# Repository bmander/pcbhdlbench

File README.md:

# pcbhdl-bench

Rosetta Code for PCB HDLs. Each case describes a circuit board in plain words: its parts, its
nets, its outline and what its layout must respect. Each toolchain writes the board in its own
language and lays it out, and every result is graded the same way, from the copper it drew.

Results: **[bmander.github.io/pcbhdlbench](https://bmander.github.io/pcbhdlbench/)**.

Modelled on [brep-bench](https://github.com/bmander/brep-bench), which does the same for B-rep
kernels.

**Status: early.** 82 cases in 11 categories, 23 of them specified down to the netlist and the
rest one-paragraph sketches. The harness grades fourteen of the checks (`parts`, `connectivity`,
`rules`, `outline`, `fixed`, `side`, `layers`, `near`, `replica`, `loop`, `apart`, `copper`,
`width`, `vias`) and refusals, which is what those 23 cases ask. Two toolchains are entered, tscircuit and netsmith, and three routers (Freerouting, fastroute and
KiCadRoutingTools) on the cases that place every part; their results are on the site.

## Why

Hardware description languages for circuit boards keep appearing (tscircuit, atopile, Zener, SKiDL,
JITX, Polymorphic Blocks), and most stop at the netlist. The step after it, from a design to a
placed and routed board, is the one now being handed to autorouters and LLM agents. The benchmarks
of that step ([a survey](landscape.json), on the site as *Prior work*) each give one canonical file
to an agent or a router. None compares the languages, and none isolates the difficulties.

## Cases

| Category | Asks |
| --- | --- |
| `basics` | Can the toolchain read a design, place, route and write a board at all |
| `placement` | Parts near a pin, on an edge, out of a keepout, under a ceiling |
| `routing` | Crossings, buses, channels, mazes, QFN and BGA fanouts |
| `power` | Width for current, pours and planes, hot loops, Kelvin and star connections |
| `highspeed` | Differential pairs, impedance, matched lengths, return paths |
| `rules` | Clearance, creepage, annular rings, edges, silkscreen |
| `outline` | Round, L-shaped and slotted boards; Uno shield, Pi HAT, M.2 |
| `reuse` | A module laid out once and used many times, congruently |
| `parametric` | Rings, grids and ladders that follow from a number |
| `unsatisfiable` | Boards that cannot be made: the right answer is a refusal |
| `integration` | Real boards, from a 555 blinker to a single-board computer |

A case is `cases/<category>/<name>.md`: a TOML header, then the description. A *specified* case's
header holds its outline, parts and nets ([`patterns.toml`](patterns.toml) has the land patterns,
[`rules.toml`](rules.toml) the rule sets); a *sketch* has only its title, layers and the checks it
would name.

## Grading, as proposed

A runner writes a KiCad `.kicad_pcb`. The harness reads its geometry and nothing else, works out
from the copper what is joined to what, and checks what the case names: always that the parts are
there, that the copper joins exactly the case's nets, that the rule set holds and that everything is
inside the outline; then, by case, fixed positions, distances, keepouts, widths, lengths, pairs,
impedance, pours, creepage, loop area, congruent replicas. **Pass** is every check. **Placed** is a
legal placement not fully routed. **Refused** ranks above **wrong**. See [SPEC.md](SPEC.md).

## Running it

```bash
(cd toolchains/tscircuit && npm install)   # tscircuit, and bun, which its CLI runs on
# netsmith, from source (it has no binary for an Intel Mac); its chips use an installed KiCad's footprints
git clone https://github.com/noahdgrant/netsmith toolchains/netsmith/upstream
(cd toolchains/netsmith/upstream && NETSMITH_SKIP_WEB=1 CARGO_TARGET_DIR=../target cargo build --release -p netsmith-cli --locked)
# the routers; all three need an installed KiCad, whose Python writes and reads Specctra and fills zones
gh release download v2.1.0 -R freerouting/freerouting -p freerouting-2.1.0.jar -D toolchains/freerouting   # runs on Java 21
gh release download v0.1.14 -R parisxmas/fastroute -p 'fastroute-0.1.14-macos-x64.tar.gz' -D toolchains/fastroute
mkdir -p toolchains/fastroute/bin && tar -xzf toolchains/fastroute/*.tar.gz -C toolchains/fastroute/bin
git clone https://github.com/drandyhaas/KiCadRoutingTools toolchains/krt/upstream
python3 -m venv toolchains/krt/venv && toolchains/krt/venv/bin/pip install numpy scipy shapely Pillow
(cd toolchains/krt/upstream && ../venv/bin/python build_router.py)
python3 harness/run.py                     # run every specified case: results/
python3 harness/site.py                    # render the board: site/
python3 -m http.server -d site             # serve it
```

The harness is Python 3.11+, standard library only; a runner needs its toolchain (tscircuit's needs
Node). `run.py --case basics/rc-lowpass` runs one case, `--toolchain NAME` one toolchain. Each
board is kept at `results/<toolchain>/<case>/board.kicad_pcb`, and the site draws it from there.

## The playground

`playground/` is a page for watching autorouters work: place pads, name nets, pick a strategy
(Lee, bidirectional, A*, Hadlock, rip-up and reroute, negotiated congestion, simulated annealing),
with tracks square or at 45°, and optionally improved afterwards by a cost of length, vias and turns, and see the search spread and the tracks
laid. The routers are a small Rust crate with no dependencies, `playground/router`, compiled to
WebAssembly behind a C ABI; the page around it is plain JavaScript and a canvas. The cases that
place every part of a two-layer board are among the boards it starts from, and so are three
boards of open hardware with their routing taken away (`playground/boards`, which says whose
they are and under what licences): an Arduino Uno R3, the Castor & Pollux synthesiser's
mainboard and the Corne keyboard.

```bash
cargo test --release --manifest-path playground/router/Cargo.toml
cargo build --release --target wasm32-unknown-unknown --manifest-path playground/router/Cargo.toml
python3 harness/site.py     # copies the page and the module to site/playground/
```

A board can be routed with no page, for timing: `python3 playground/boards/floats.py
playground/boards/corne-keyboard.json /tmp/corne.f32`, then `cargo run --release --example route
--manifest-path playground/router/Cargo.toml -- /tmp/corne.f32 6 1 300` (the strategy's number, 1
for diagonal steps, and the seconds to go on for).

These are teaching routers on a coarse grid, not entrants: they are not on the routers' board.

## Adding a toolchain

Write a runner (`<command> <case id> <out dir>`, see [SPEC.md](SPEC.md#a-runner)) and an
implementation of each specified case under `toolchains/<name>/`, and give the toolchain's entry
in `toolchains.json` its `command`, `version` and `source`. `toolchains/tscircuit` and
`toolchains/netsmith` are the two to copy from. A toolchain that numbers its own parts says which
is which in its `result.json` (`refs`), as netsmith's runner does.

## Open questions

- **Who is entered.** As written, a toolchain: a language with whatever places and routes for it,
  an LLM agent included. The cases would serve as well for agents alone, each given the case and
  any language it likes.
- **Land patterns.** The bench defines its own in `patterns.toml` and checks pads, not names. A
  large case will need a few hundred; importing a subset of KiCad's library by name may be saner.
- **What "placed" is worth**, when most of these languages cannot route.
- **Electrical checks beyond geometry.** Impedance and creepage are computed from geometry here;
  nothing is simulated.

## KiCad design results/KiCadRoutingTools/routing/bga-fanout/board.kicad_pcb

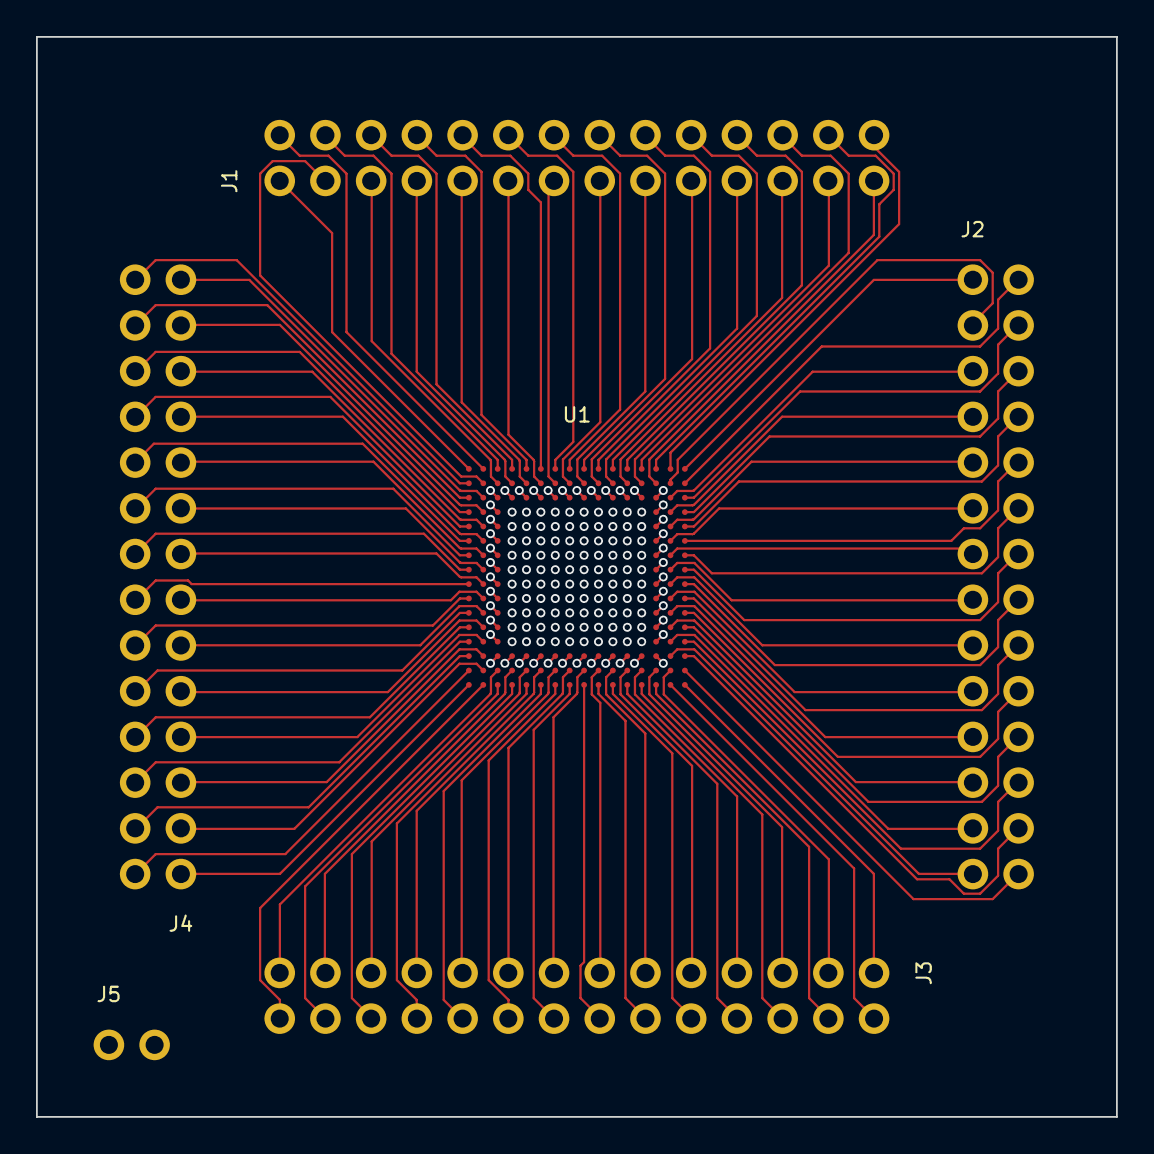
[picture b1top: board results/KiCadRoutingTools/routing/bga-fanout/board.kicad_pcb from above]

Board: 4 copper layers, 60.0 x 60.0 mm, 6 parts (0 on the bottom side), 114 nets.

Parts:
J1, J2, J3, J4: HDR_2x14_2.54
J5: HDR_1x2_2.54
U1: BGA-256

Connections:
A1: J1.1, U1.A1
A2: J1.2, U1.A2
A3: J1.4, U1.A3
A4: J1.6, U1.A4
A5: J1.8, U1.A5
A6: J1.10, U1.A6
A7: J1.12, U1.A7
A8: J1.14, U1.A8
A9: J1.16, U1.A9
A10: J1.18, U1.A10
A11: J1.20, U1.A11
A12: J1.22, U1.A12
A13: J1.24, U1.A13
A14: J1.26, U1.A14
A15: J1.28, U1.A15
A16: J2.1, U1.A16
B1: J4.28, U1.B1
B2: J1.3, U1.B2
B3: J1.5, U1.B3
B4: J1.7, U1.B4
B5: J1.9, U1.B5
B6: J1.11, U1.B6
B7: J1.13, U1.B7
B8: J1.15, U1.B8
B9: J1.17, U1.B9
B10: J1.19, U1.B10
B11: J1.21, U1.B11
B12: J1.23, U1.B12
B13: J1.25, U1.B13
B14: J1.27, U1.B14
B15: J2.3, U1.B15
B16: J2.2, U1.B16
C1: J4.26, U1.C1
C2: J4.27, U1.C2
C15: J2.5, U1.C15
C16: J2.4, U1.C16
D1: J4.24, U1.D1
D2: J4.25, U1.D2
D15: J2.7, U1.D15
D16: J2.6, U1.D16
E1: J4.22, U1.E1
E2: J4.23, U1.E2
E15: J2.9, U1.E15
E16: J2.8, U1.E16
F1: J4.20, U1.F1
F2: J4.21, U1.F2
F15: J2.11, U1.F15
F16: J2.10, U1.F16
G1: J4.18, U1.G1
G2: J4.19, U1.G2
G15: J2.13, U1.G15
G16: J2.12, U1.G16
GND: J5.2, U1.C3, U1.C5, U1.C7, U1.C9, U1.C11, U1.C13, U1.D4, U1.D6, U1.D8, U1.D10, U1.D12, U1.D14, U1.E3, U1.E5, U1.E7, U1.E9, U1.E11, U1.E13, U1.F4, U1.F6, U1.F8, U1.F10, U1.F12, U1.F14, U1.G3, U1.G5, U1.G7, U1.G9, U1.G11, U1.G13, U1.H4, U1.H6, U1.H8, U1.H10, U1.H12, U1.H14, U1.J3, U1.J5, U1.J7, U1.J9, U1.J11, U1.J13, U1.K4, U1.K6, U1.K8, U1.K10, U1.K12, U1.K14, U1.L3, U1.L5, U1.L7, U1.L9, U1.L11, U1.L13, U1.M4, U1.M6, U1.M8, U1.M10, U1.M12, U1.M14, U1.N3, U1.N5, U1.N7, U1.N9, U1.N11, U1.N13, U1.P4, U1.P6, U1.P8, U1.P10, U1.P12, U1.P14
H1: J4.16, U1.H1
H2: J4.17, U1.H2
H15: J2.15, U1.H15
H16: J2.14, U1.H16
J1: J4.14, U1.J1
J2: J4.15, U1.J2
J15: J2.17, U1.J15
J16: J2.16, U1.J16
K1: J4.12, U1.K1
K2: J4.13, U1.K2
K15: J2.19, U1.K15
K16: J2.18, U1.K16
L1: J4.10, U1.L1
L2: J4.11, U1.L2
L15: J2.21, U1.L15
L16: J2.20, U1.L16
M1: J4.8, U1.M1
M2: J4.9, U1.M2
M15: J2.23, U1.M15
M16: J2.22, U1.M16
N1: J4.6, U1.N1
N2: J4.7, U1.N2
N15: J2.25, U1.N15
N16: J2.24, U1.N16
P1: J4.4, U1.P1
P2: J4.5, U1.P2
P15: J2.27, U1.P15
P16: J2.26, U1.P16
R1: J4.2, U1.R1
R2: J4.3, U1.R2
R3: J3.27, U1.R3
R4: J3.25, U1.R4
R5: J3.23, U1.R5
R6: J3.21, U1.R6
R7: J3.19, U1.R7
R8: J3.17, U1.R8
R9: J3.15, U1.R9
R10: J3.13, U1.R10
R11: J3.11, U1.R11
R12: J3.9, U1.R12
R13: J3.7, U1.R13
R14: J3.5, U1.R14
R15: J3.3, U1.R15
R16: J2.28, U1.R16
T1: J4.1, U1.T1
T2: J3.28, U1.T2
T3: J3.26, U1.T3
T4: J3.24, U1.T4
T5: J3.22, U1.T5
T6: J3.20, U1.T6
T7: J3.18, U1.T7
T8: J3.16, U1.T8
T9: J3.14, U1.T9
T10: J3.12, U1.T10
T11: J3.10, U1.T11
T12: J3.8, U1.T12
T13: J3.6, U1.T13
T14: J3.4, U1.T14
T15: J3.2, U1.T15
T16: J3.1, U1.T16
VCC: J5.1, U1.C4, U1.C6, U1.C8, U1.C10, U1.C12, U1.C14, U1.D3, U1.D5, U1.D7, U1.D9, U1.D11, U1.D13, U1.E4, U1.E6, U1.E8, U1.E10, U1.E12, U1.E14, U1.F3, U1.F5, U1.F7, U1.F9, U1.F11, U1.F13, U1.G4, U1.G6, U1.G8, U1.G10, U1.G12, U1.G14, U1.H3, U1.H5, U1.H7, U1.H9, U1.H11, U1.H13, U1.J4, U1.J6, U1.J8, U1.J10, U1.J12, U1.J14, U1.K3, U1.K5, U1.K7, U1.K9, U1.K11, U1.K13, U1.L4, U1.L6, U1.L8, U1.L10, U1.L12, U1.L14, U1.M3, U1.M5, U1.M7, U1.M9, U1.M11, U1.M13, U1.N4, U1.N6, U1.N8, U1.N10, U1.N12, U1.N14, U1.P3, U1.P5, U1.P7, U1.P9, U1.P11, U1.P13

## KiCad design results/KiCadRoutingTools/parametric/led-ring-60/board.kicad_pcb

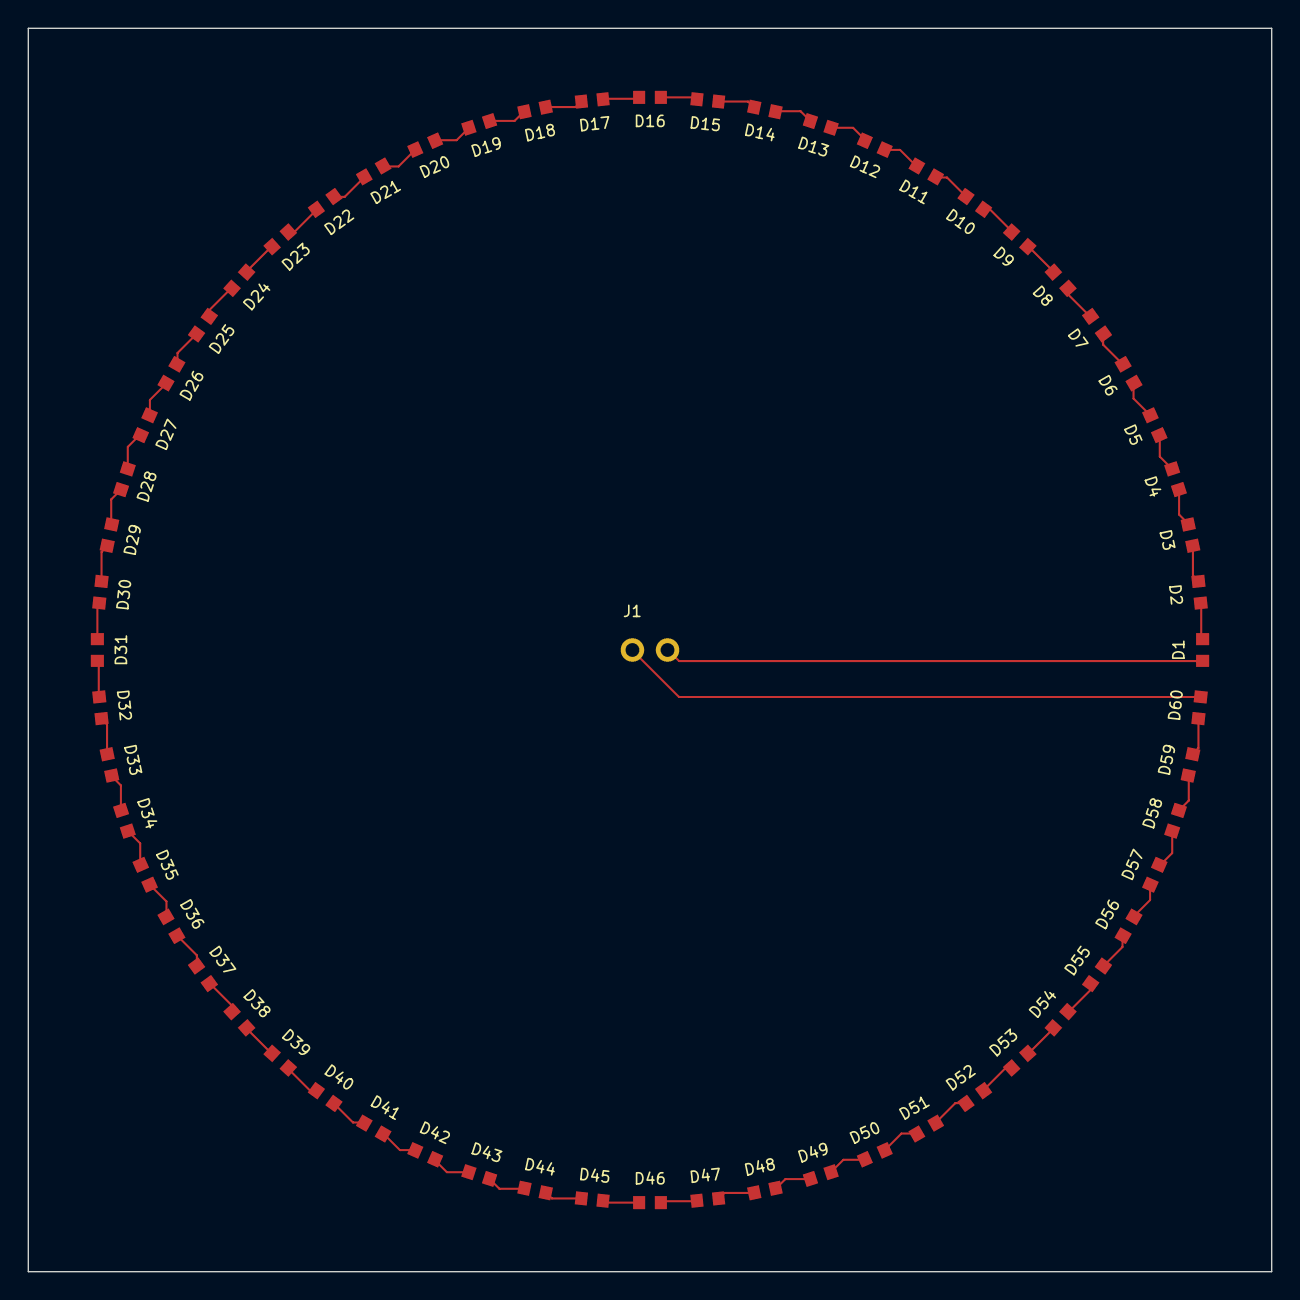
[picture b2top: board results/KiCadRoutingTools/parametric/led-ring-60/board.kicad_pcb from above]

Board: 2 copper layers, 90.0 x 90.0 mm, 61 parts (0 on the bottom side), 61 nets.

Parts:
D1, D2, D3, D4, D5, D6, D7, D8, D9, D10, D11, D12, D13, D14, D15, D16, D17, D18, D19, D20, D21, D22, D23, D24, D25, D26, D27, D28, D29, D30, D31, D32, D33, D34, D35, D36, D37, D38, D39, D40, D41, D42, D43, D44, D45, D46, D47, D48, D49, D50, D51, D52, D53, D54, D55, D56, D57, D58, D59, D60: LED_0603
J1: HDR_1x2_2.54

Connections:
GND: D1.K, J1.2
L1: D1.A, D2.K
L2: D2.A, D3.K
L3: D3.A, D4.K
L4: D4.A, D5.K
L5: D5.A, D6.K
L6: D6.A, D7.K
L7: D7.A, D8.K
L8: D8.A, D9.K
L9: D9.A, D10.K
L10: D10.A, D11.K
L11: D11.A, D12.K
L12: D12.A, D13.K
L13: D13.A, D14.K
L14: D14.A, D15.K
L15: D15.A, D16.K
L16: D16.A, D17.K
L17: D17.A, D18.K
L18: D18.A, D19.K
L19: D19.A, D20.K
L20: D20.A, D21.K
L21: D21.A, D22.K
L22: D22.A, D23.K
L23: D23.A, D24.K
L24: D24.A, D25.K
L25: D25.A, D26.K
L26: D26.A, D27.K
L27: D27.A, D28.K
L28: D28.A, D29.K
L29: D29.A, D30.K
L30: D30.A, D31.K
L31: D31.A, D32.K
L32: D32.A, D33.K
L33: D33.A, D34.K
L34: D34.A, D35.K
L35: D35.A, D36.K
L36: D36.A, D37.K
L37: D37.A, D38.K
L38: D38.A, D39.K
L39: D39.A, D40.K
L40: D40.A, D41.K
L41: D41.A, D42.K
L42: D42.A, D43.K
L43: D43.A, D44.K
L44: D44.A, D45.K
L45: D45.A, D46.K
L46: D46.A, D47.K
L47: D47.A, D48.K
L48: D48.A, D49.K
L49: D49.A, D50.K
L50: D50.A, D51.K
L51: D51.A, D52.K
L52: D52.A, D53.K
L53: D53.A, D54.K
L54: D54.A, D55.K
L55: D55.A, D56.K
L56: D56.A, D57.K
L57: D57.A, D58.K
L58: D58.A, D59.K
L59: D59.A, D60.K
VIN: D60.A, J1.1

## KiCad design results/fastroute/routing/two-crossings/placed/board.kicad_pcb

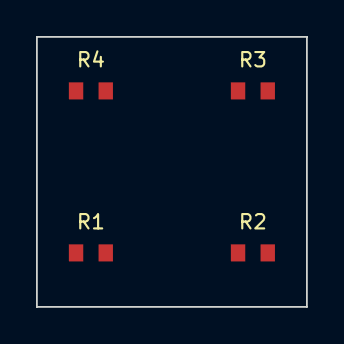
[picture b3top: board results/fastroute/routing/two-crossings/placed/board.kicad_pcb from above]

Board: 2 copper layers, 15.0 x 15.0 mm, 4 parts (0 on the bottom side), 2 nets, no tracks yet.

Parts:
R1, R2, R3, R4: R_0603

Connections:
A: R1.2, R3.1
B: R2.1, R4.2
